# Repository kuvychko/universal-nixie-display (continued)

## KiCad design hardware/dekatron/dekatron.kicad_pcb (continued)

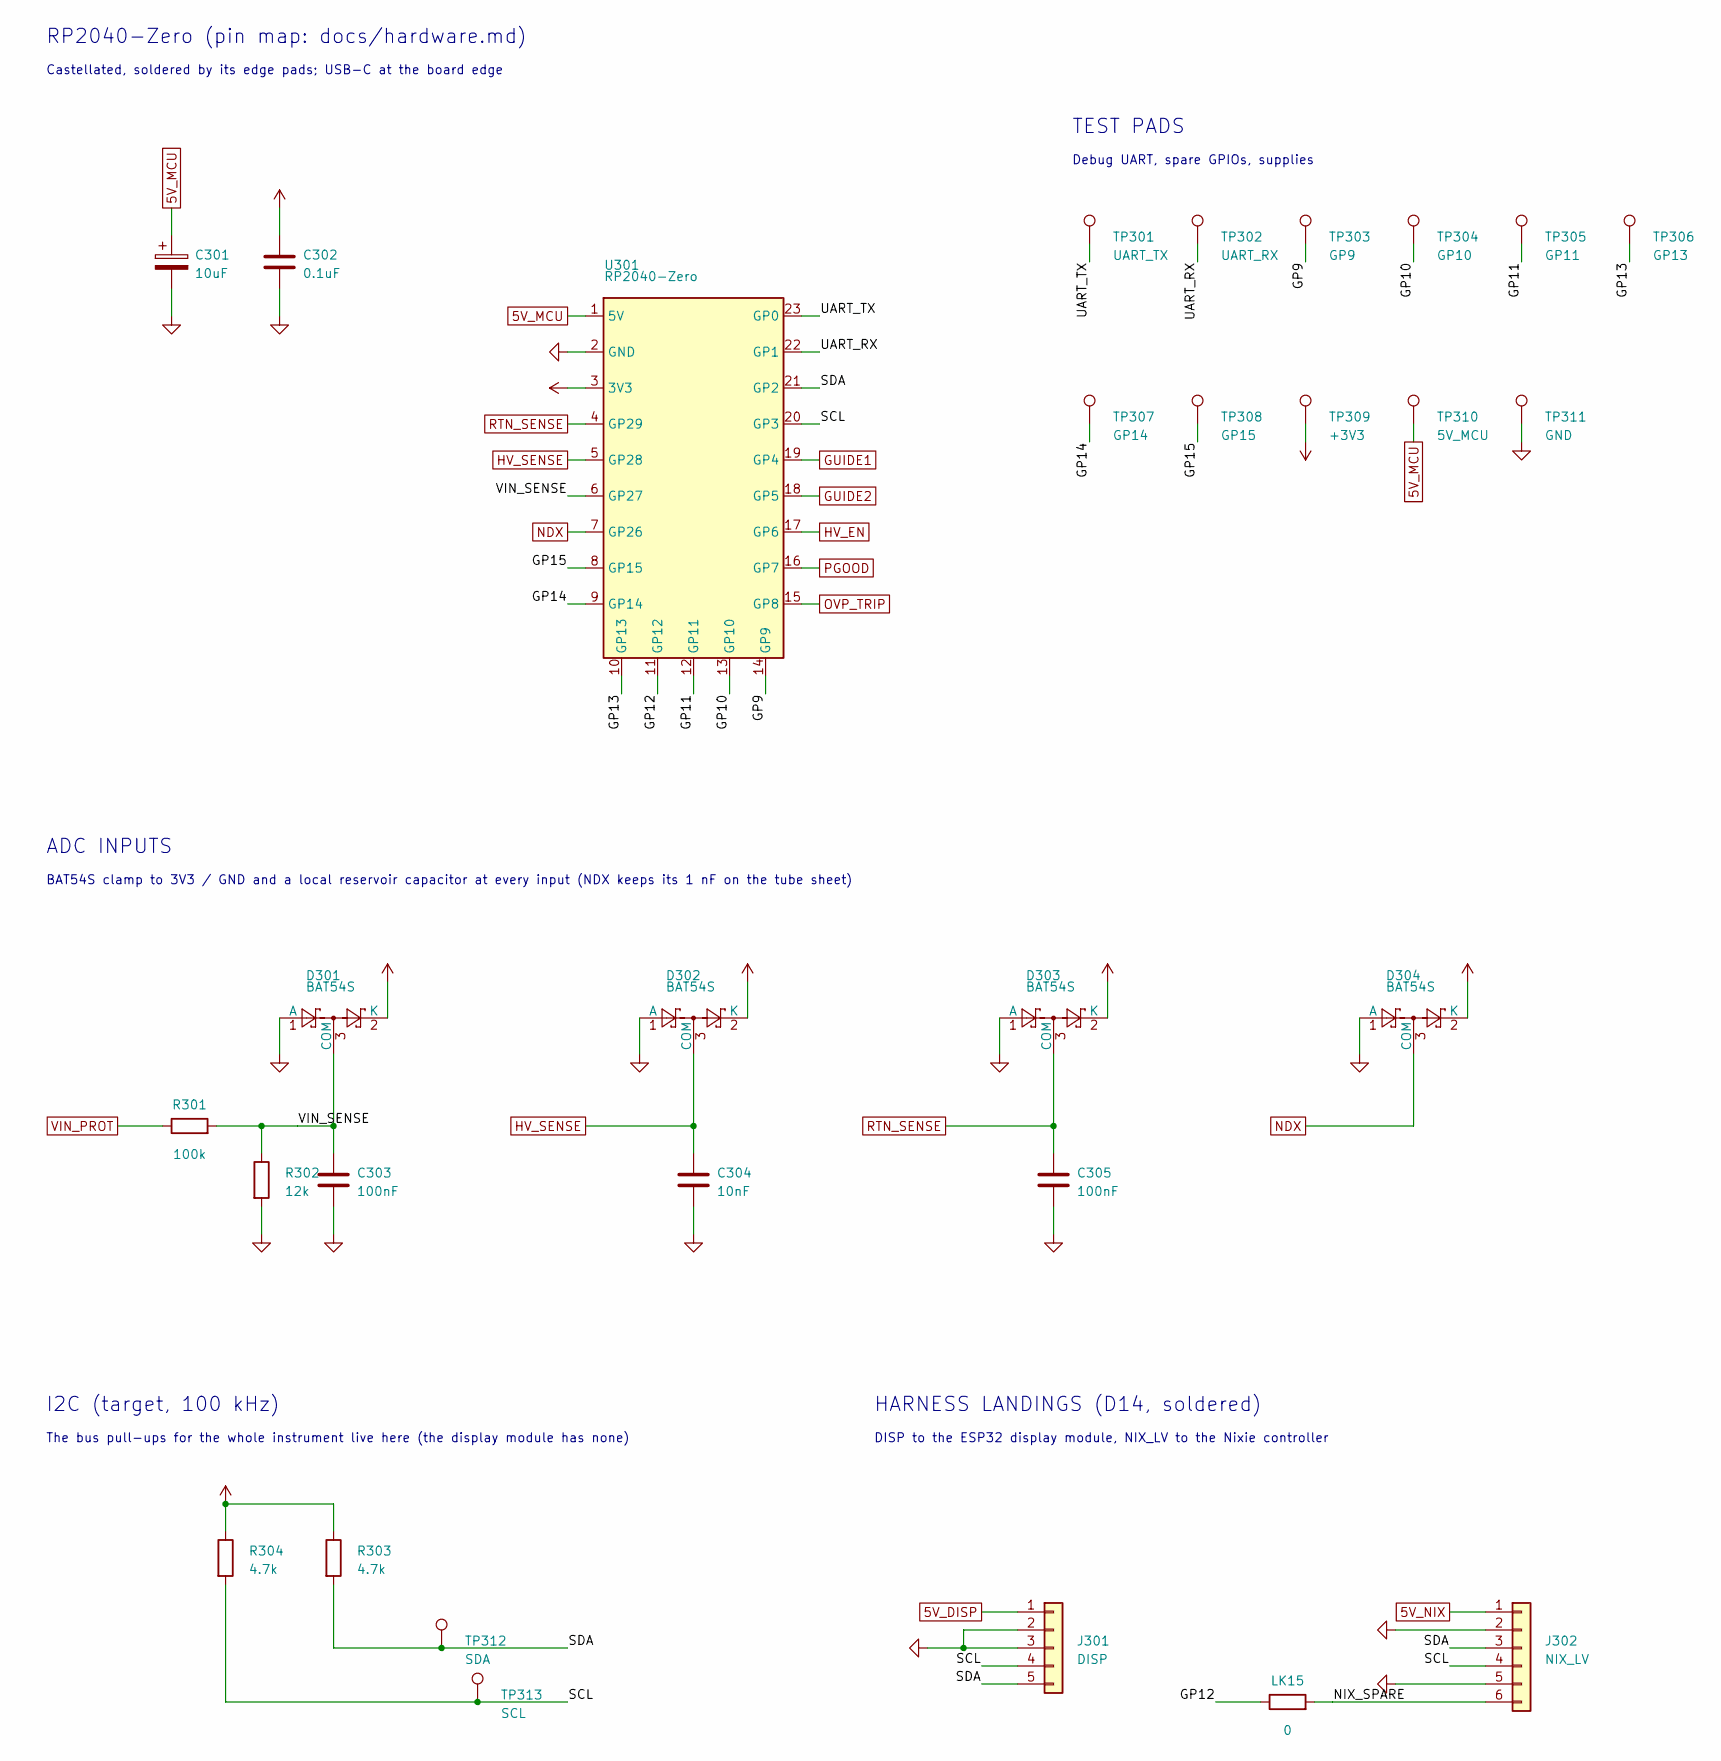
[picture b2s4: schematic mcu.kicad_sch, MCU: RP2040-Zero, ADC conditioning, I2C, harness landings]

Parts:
C301: 10uF; CP_EIA-3216-18_Kemet-A; Rating 16 V tantalum, 1.5 ohm ESR; MPN F911C106MAAAJ6
C302: 0.1uF; C_1206_3216Metric; Rating 50 V X7R; MPN CC1206JPX7R9BB104
C303, C305: 100nF; C_1206_3216Metric; Rating 25 V X7R; MPN CC1206JPX7R9BB104
C304: 10nF; C_1206_3216Metric; Rating 25 V X7R; MPN 12063C103JAT2A
D301, D302, D303, D304: BAT54S; SOT-23; Rating 30 V Schottky pair; MPN BAT54S RFG
J301: DISP; SolderWire-0.5sqmm_1x05_P4.8mm_D0.9mm_OD2.3mm
J302: NIX_LV; SolderWire-0.5sqmm_1x06_P4.8mm_D0.9mm_OD2.3mm
LK15: 0; R_1206_3216Metric
R301: 100k; R_1206_3216Metric
R302: 12k; R_1206_3216Metric; Rating 1 %; MPN ERJ-8ENF1202V
R303, R304: 4.7k; R_1206_3216Metric
TP301: UART_TX; TestPoint_THTPad_D1.5mm_Drill0.7mm
TP302: UART_RX; TestPoint_THTPad_D1.5mm_Drill0.7mm
TP303: GP9; TestPoint_THTPad_D1.5mm_Drill0.7mm
TP304: GP10; TestPoint_THTPad_D1.5mm_Drill0.7mm
TP305: GP11; TestPoint_THTPad_D1.5mm_Drill0.7mm
TP306: GP13; TestPoint_THTPad_D1.5mm_Drill0.7mm
TP307: GP14; TestPoint_THTPad_D1.5mm_Drill0.7mm
TP308: GP15; TestPoint_THTPad_D1.5mm_Drill0.7mm
TP309: +3V3; TestPoint_THTPad_D1.5mm_Drill0.7mm
TP310: 5V_MCU; TestPoint_THTPad_D1.5mm_Drill0.7mm
TP311: GND; TestPoint_THTPad_D1.5mm_Drill0.7mm
TP312: SDA; TestPoint_THTPad_D1.5mm_Drill0.7mm
TP313: SCL; TestPoint_THTPad_D1.5mm_Drill0.7mm
U301: RP2040-Zero; RP2040-Zero_Castellated; Rating headerless, castellated; MPN RP2040-Zero

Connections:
5V_DISP: J301.1; also elsewhere on the board
5V_MCU: C301.1, TP310.1, U301.1 (5V); also elsewhere on the board
5V_NIX: J302.1; also elsewhere on the board
+3V3: C302.1, D301.2 (K), D302.2 (K), D303.2 (K), D304.2 (K), R303.1, R304.1, TP309.1, U301.3 (3V3); also elsewhere on the board
/mcu/GP9: TP303.1, U301.14 (GP9)
/mcu/GP10: TP304.1, U301.13 (GP10)
/mcu/GP11: TP305.1, U301.12 (GP11)
/mcu/GP12: LK15.1, U301.11 (GP12)
/mcu/GP13: TP306.1, U301.10 (GP13)
/mcu/GP14: TP307.1, U301.9 (GP14)
/mcu/GP15: TP308.1, U301.8 (GP15)
/mcu/NIX_SPARE: J302.6, LK15.2
/mcu/SCL: J301.4, J302.4, R304.2, TP313.1, U301.20 (GP3)
/mcu/SDA: J301.5, J302.3, R303.2, TP312.1, U301.21 (GP2)
/mcu/UART_RX: TP302.1, U301.22 (GP1)
/mcu/UART_TX: TP301.1, U301.23 (GP0)
/mcu/VIN_SENSE: C303.1, D301.3 (COM), R301.2, R302.1, U301.6 (GP27)
GND: C301.2, C302.2, C303.2, C304.2, C305.2, D301.1 (A), D302.1 (A), D303.1 (A), D304.1 (A), J301.2, J301.3, J302.2, J302.5, R302.2, TP311.1, U301.2 (GND); also elsewhere on the board
GUIDE1: U301.19 (GP4); also elsewhere on the board
GUIDE2: U301.18 (GP5); also elsewhere on the board
HV_EN: U301.17 (GP6); also elsewhere on the board
HV_SENSE: C304.1, D302.3 (COM), U301.5 (GP28); also elsewhere on the board
NDX: D304.3 (COM), U301.7 (GP26); also elsewhere on the board
OVP_TRIP: U301.15 (GP8); also elsewhere on the board
PGOOD: U301.16 (GP7); also elsewhere on the board
RTN_SENSE: C305.1, D303.3 (COM), U301.4 (GP29); also elsewhere on the board
VIN_PROT: R301.1; also elsewhere on the board

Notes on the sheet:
RP2040-Zero (pin map: docs/hardware.md)
Castellated, soldered by its edge pads; USB-C at the board edge
TEST PADS
Debug UART, spare GPIOs, supplies
ADC INPUTS
BAT54S clamp to 3V3 / GND and a local reservoir capacitor at every input (NDX keeps its 1 nF on the tube sheet)
I2C (target, 100 kHz)
The bus pull-ups for the whole instrument live here (the display module has none)
HARNESS LANDINGS (D14, soldered)
DISP to the ESP32 display module, NIX_LV to the Nixie controller

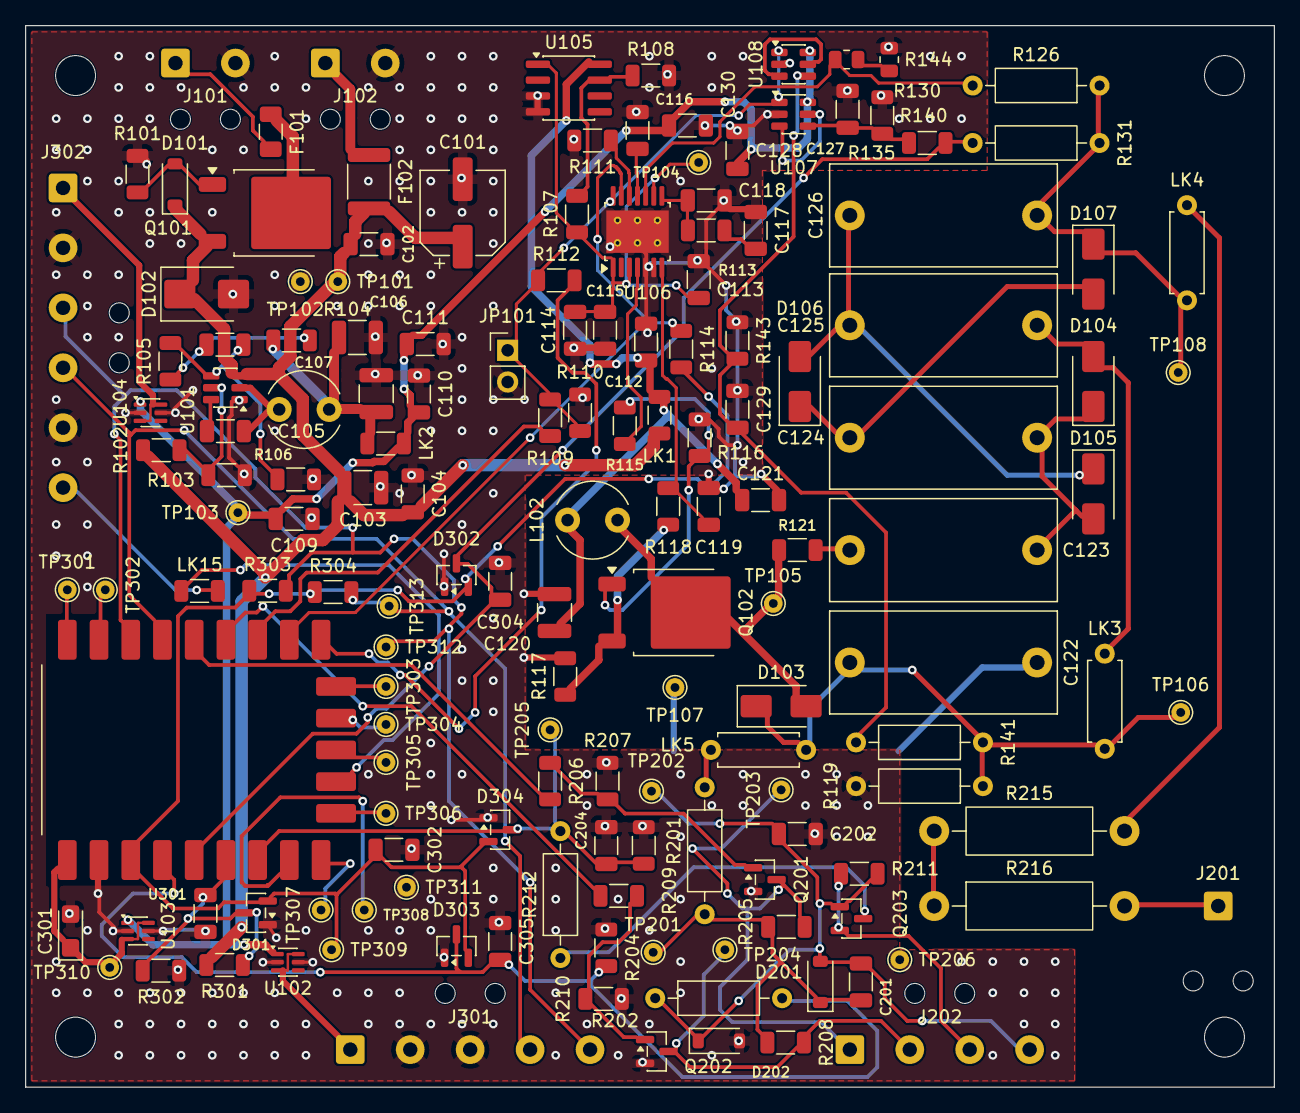
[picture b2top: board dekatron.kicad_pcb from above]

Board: 2 copper layers, 100.0 x 85.0 mm, 165 parts (0 on the bottom side), 76 nets.

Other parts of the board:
H1, H2, H3, H4: MountingHole_3.2mm_M3
TIE_J101, TIE_J102, TIE_J201, TIE_J202, TIE_J301, TIE_J302: cable tie

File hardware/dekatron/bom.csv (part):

Reference,Value,Function,Manufacturer,MPN,Rating,Footprint,Fit
C101,100uF 35V,"Input bulk, damps hot-plug ringing",Panasonic,EEE-FK1V101XP,"35 V, 340 mohm ESR",Capacitor_SMD:CP_Elec_6.3x7.7,
C102,0.1uF,Input HF bypass,Yageo,CC1206JPX7R9BB104,50 V X7R,Capacitor_SMD:C_1206_3216Metric,
C103,10uF 35V,Buck input,Yageo,CC1210KKX7RGBB106,35 V X7R,Capacitor_SMD:C_1210_3225Metric,
C104,0.1uF,Buck input HF,Yageo,CC1206JPX7R9BB104,50 V X7R,Capacitor_SMD:C_1206_3216Metric,
C105,0.1uF,Buck bootstrap,Yageo,CC1206JPX7R9BB104,25 V X7R,Capacitor_SMD:C_1206_3216Metric,
C106,22uF 25V,Buck output,Taiyo Yuden,MBAST32MSB7226KPNA18,25 V X7R,Capacitor_SMD:C_1210_3225Metric,
C107,22uF 25V,Buck output,Taiyo Yuden,MBAST32MSB7226KPNA18,25 V X7R,Capacitor_SMD:C_1210_3225Metric,
C108,75pF,Buck feed-forward,KYOCERA AVX,12065A750JAT2A,50 V C0G,Capacitor_SMD:C_1206_3216Metric,
C109,0.1uF,U102 input bypass,Yageo,CC1206JPX7R9BB104,50 V X7R,Capacitor_SMD:C_1206_3216Metric,
C110,0.1uF,U103 input bypass,Yageo,CC1206JPX7R9BB104,50 V X7R,Capacitor_SMD:C_1206_3216Metric,
C111,0.1uF,U104 input bypass,Yageo,CC1206JPX7R9BB104,50 V X7R,Capacitor_SMD:C_1206_3216Metric,
C112,1uF 35V,LDO input,KYOCERA AVX,1206DC105MAT2A,35 V X7R,Capacitor_SMD:C_1206_3216Metric,
C113,2.2uF,LDO output,Yageo,CS1206KKX7R8BB225,25 V X7R,Capacitor_SMD:C_1206_3216Metric,
C114,1uF,LM5156 BIAS/VCC bypass,KYOCERA AVX,1206DC105MAT2A,25 V X7R,Capacitor_SMD:C_1206_3216Metric,
C115,0.1uF,LM5156 BIAS/VCC HF,Yageo,CC1206JPX7R9BB104,50 V X7R,Capacitor_SMD:C_1206_3216Metric,
C116,47nF,Soft-start,Yageo,CC1206KRX7R8BB473,25 V X7R,Capacitor_SMD:C_1206_3216Metric,
C117,10nF,Compensation C,KYOCERA AVX,12063C103JAT2A,25 V X7R,Capacitor_SMD:C_1206_3216Metric,
C118,100pF,Compensation HF,KEMET,C1206C101K5GAC7210,50 V C0G,Capacitor_SMD:C_1206_3216Metric,
C119,470pF,CS filter C (pump surge),Walsin,1206B471K500CT,50 V C0G,Capacitor_SMD:C_1206_3216Metric,
C120,10uF 35V,Boost input,Yageo,CC1210KKX7RGBB106,35 V X7R,Capacitor_SMD:C_1210_3225Metric,
C121,0.1uF,Boost input HF,Yageo,CC1206JPX7R9BB104,50 V X7R,Capacitor_SMD:C_1206_3216Metric,
C122,0.47uF 400V,Tripler stack C1 (V_b),WIMA,MKS4G034704F00MSSD,400 V PET film,Capacitor_THT:C_Rect_L18.0mm_W8.0mm_P15.00mm_FKS3_FKP3,
C123,0.47uF 400V,Tripler pump CP1,WIMA,MKS4G034704F00MSSD,400 V PET film,Capacitor_THT:C_Rect_L18.0mm_W8.0mm_P15.00mm_FKS3_FKP3,
C124,0.47uF 400V,Tripler pump CP2,WIMA,MKS4G034704F00MSSD,400 V PET film,Capacitor_THT:C_Rect_L18.0mm_W8.0mm_P15.00mm_FKS3_FKP3,
C125,0.47uF 400V,Tripler stack C2,WIMA,MKS4G034704F00MSSD,400 V PET film,Capacitor_THT:C_Rect_L18.0mm_W8.0mm_P15.00mm_FKS3_FKP3,
C126,0.47uF 400V,Tripler stack C3,WIMA,MKS4G034704F00MSSD,400 V PET film,Capacitor_THT:C_Rect_L18.0mm_W8.0mm_P15.00mm_FKS3_FKP3,
C127,1nF,OVP sense filter,Walsin,1206N102K501CT,50 V C0G,Capacitor_SMD:C_1206_3216Metric,
C128,0.1uF,U107 bypass,Yageo,CC1206JPX7R9BB104,50 V X7R,Capacitor_SMD:C_1206_3216Metric,
C129,1nF,V_b OVP sense filter,Walsin,1206N102K501CT,50 V C0G,Capacitor_SMD:C_1206_3216Metric,
C130,0.1uF,U108 bypass,Yageo,CC1206JPX7R9BB104,50 V X7R,Capacitor_SMD:C_1206_3216Metric,
C201,0.1uF 100V,G+ to RTN bypass,Yageo,AC1206KKX7R0BB104,100 V X7R,Capacitor_SMD:C_1206_3216Metric,
C202,1uF 100V,RTN bypass: absorbs tube and guide current steps,KEMET,C1206C105M1RACAUTO,100 V X7R,Capacitor_SMD:C_1206_3216Metric,
C204,1nF,Index filter (tau 12 us),Walsin,1206N102K501CT,50 V C0G,Capacitor_SMD:C_1206_3216Metric,
C301,10uF,5V_MCU bulk at the module,KYOCERA AVX,F911C106MAAAJ6,"16 V tantalum, 1.5 ohm ESR",Capacitor_Tantalum_SMD:CP_EIA-3216-18_Kemet-A,
C302,0.1uF,3V3 bypass,Yageo,CC1206JPX7R9BB104,50 V X7R,Capacitor_SMD:C_1206_3216Metric,
C303,100nF,VIN_SENSE ADC sampling reservoir,Yageo,CC1206JPX7R9BB104,25 V X7R,Capacitor_SMD:C_1206_3216Metric,
C304,10nF,HV_SENSE ADC sampling reservoir,KYOCERA AVX,12063C103JAT2A,25 V X7R,Capacitor_SMD:C_1206_3216Metric,
C305,100nF,RTN_SENSE ADC sampling reservoir,Yageo,CC1206JPX7R9BB104,25 V X7R,Capacitor_SMD:C_1206_3216Metric,
D101,BZT52C10,"Q101 gate-source clamp, -10 V",Diotec Semiconductor,BZT52C10,,Diode_SMD:D_SOD-123,
D102,SMBJ15A,"Input TVS, unidirectional",Semtech,SMBJ15A,"15 V standoff, 24.4 V clamp",Diode_SMD:D_SMB,
D103,ES1J,Boost diode,Diotec Semiconductor,ES1J,"600 V, 1 A, 35 ns",Diode_SMD:D_SMA,
D104,ES1J,Tripler diode,Diotec Semiconductor,ES1J,"600 V, 1 A, 35 ns",Diode_SMD:D_SMA,
D105,ES1J,Tripler diode,Diotec Semiconductor,ES1J,"600 V, 1 A, 35 ns",Diode_SMD:D_SMA,
D106,ES1J,Tripler diode,Diotec Semiconductor,ES1J,"600 V, 1 A, 35 ns",Diode_SMD:D_SMA,
D107,ES1J,Tripler diode,Diotec Semiconductor,ES1J,"600 V, 1 A, 35 ns",Diode_SMD:D_SMA,
D201,39V,G+ above RTN: guide bias 39 V,Taiwan Semiconductor,MMSZ5259BH RHG,"39 V, 500 mW",Diode_SMD:D_SOD-123,
D202,51V,RTN shunt regulator: sinks tube current,onsemi,MMSZ5262BT1G,"51 V, 500 mW",Diode_SMD:D_SOD-123,
D301,BAT54S,VIN_SENSE clamp to 3V3 / GND,Taiwan Semiconductor,BAT54S RFG,30 V Schottky pair,Package_TO_SOT_SMD:SOT-23,
D302,BAT54S,HV_SENSE clamp to 3V3 / GND,Taiwan Semiconductor,BAT54S RFG,30 V Schottky pair,Package_TO_SOT_SMD:SOT-23,
D303,BAT54S,RTN_SENSE clamp to 3V3 / GND,Taiwan Semiconductor,BAT54S RFG,30 V Schottky pair,Package_TO_SOT_SMD:SOT-23,
D304,BAT54S,NDX clamp to 3V3 / GND,Taiwan Semiconductor,BAT54S RFG,30 V Schottky pair,Package_TO_SOT_SMD:SOT-23,
F101,2A Slo-Blo,Input fuse,Littelfuse,0468002.NRHF,"2 A, 63 V, I2t 0.506 A2s",Fuse:Fuse_1206_3216Metric,
F102,0.75A,Nixie HV module branch fuse,Littelfuse,1812L075/33DR,"0.75 A hold, 33 V",Fuse:Fuse_1812_4532Metric,
J101,PWR_IN,Harness landing PWR_IN: +12V_IN from panel switch / barrel jack; GND,,,,Connector_Wire:SolderWire-0.5sqmm_1x02_P4.8mm_D0.9mm_OD2.3mm,
J102,NIX_12V,Harness landing NIX_12V to the purchased Nixie HV module,,,,Connector_Wire:SolderWire-0.5sqmm_1x02_P4.8mm_D0.9mm_OD2.3mm,
J201,TUBE_ANODE,"Tube harness: anode (pin 8), 600 V wire, kept >= 3 mm from other pads",,,,Connector_Wire:SolderWire-0.5sqmm_1x01_D0.9mm_OD2.3mm,
J202,TUBE,"Tube harness: G1 (pin 5), G2 (10), K1 index (13), RTN = K0, K2-K9 tied at the socket",,,,Connector_Wire:SolderWire-0.5sqmm_1x04_P4.8mm_D0.9mm_OD2.3mm,
J301,DISP,"Harness DISP: 5V (P1 5V), GND (P1 GND), GND (3V3-plug GND), SCL (IO18), SDA (IO27)",,,,Connector_Wire:SolderWire-0.5sqmm_1x05_P4.8mm_D0.9mm_OD2.3mm,
J302,NIX_LV,Harness NIX_LV to the Nixie controller board,,,,Connector_Wire:SolderWire-0.5sqmm_1x06_P4.8mm_D0.9mm_OD2.3mm,
JP101,HV_INHIBIT,HV inhibit jumper (D11): shunt fitted holds EN/UVLO low,,,,Connector_PinHeader_2.54mm:PinHeader_1x02_P2.54mm_Vertical,
L101,15uH,Buck inductor,,"(kit, 6 x 8 mm radial)",Rated 1.31 A; limits the 5 V rail to ~1.3 A,Inductor_THT:L_Radial_D6.0mm_P4.00mm,
L102,100uH,HV boost inductor,,"(kit, 6 x 8 mm radial)","Rated 0.71 A, DCR 0.35 ohm, 4 mm pitch",Inductor_THT:L_Radial_D6.0mm_P4.00mm,
LK1,0,"D11 link L1: 12 V to the HV section (0 ohm, remove to open)",,,,Resistor_SMD:R_1206_3216Metric,
LK2,0,"D11 link L2: buck output to board 5 V (0 ohm, remove to open)",,,,Resistor_SMD:R_1206_3216Metric,
LK3,LINK,"D11 link L3: V_b to the tripler DC column (fault isolation; never powered open) (wire link, desolder to open)",,,,Resistor_THT:R_Axial_DIN0207_L6.3mm_D2.5mm_P7.62mm_Horizontal,
LK4,LINK,"D11 link L4: tripler output to the anode string (wire link, desolder to open)",,,,Resistor_THT:R_Axial_DIN0207_L6.3mm_D2.5mm_P7.62mm_Horizontal,
LK5,LINK,"D11 link L5: V_b to the G+/RTN regulators (wire link, desolder to open)",,,,Resistor_THT:R_Axial_DIN0207_L6.3mm_D2.5mm_P7.62mm_Horizontal,
LK15,0,"GP12 to the NIX_LV spare wire (0 ohm, fit when used)",,,,Resistor_SMD:R_1206_3216Metric,
Q101,IPD50P04P4L-11,Reverse-polarity protection,Infineon,IPD50P04P4L11ATMA2,"-40 V, 10.6 mohm, 200 A pulsed, VGS +5/-16 V",Package_TO_SOT_SMD:TO-252-2,
Q102,IPD70R1K4P7S,HV boost switch,Infineon,IPD70R1K4P7SAUMA1,"700 V, 1.4 ohm at 10 V, VGS +/-16 V",Package_TO_SOT_SMD:TO-252-2,
Q201,MMBTA42,Guide 1 driver,Diotec Semiconductor,MMBTA42,300 V NPN,Package_TO_SOT_SMD:SOT-23,
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
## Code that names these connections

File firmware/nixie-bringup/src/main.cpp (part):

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#include <Adafruit_NeoPixel.h>
#include <Wire.h>

static const uint8_t PIN_NIX12_EN = 0;  // Q102 base -> Q101 gate; R104 holds it off in reset
static const uint8_t PIN_SPARE = 1;     // NIX_SPARE, hardware pull-down; read only
static const uint8_t PIN_MAIN_SDA = 2;  // main bus (I2C1 target in the product): left as inputs
static const uint8_t PIN_MAIN_SCL = 3;
static const uint8_t PIN_WWVB_SDA = 4;  // I2C0, ES100 only (10k pull-ups on the carrier)
static const uint8_t PIN_WWVB_SCL = 5;
static const uint8_t PIN_WWVB_EN = 6;   // R308 10k pull-down: ES100 in shutdown in reset
static const uint8_t PIN_WWVB_IRQ = 7;  // R307 10k pull-up, active low
static const uint8_t PIN_BL = 8;        // DRV_BL via U302; R301 / R310 pull-downs: dark in reset
static const uint8_t PIN_LE = 9;        // DRV_LE via U302: high loads the latches
static const uint8_t PIN_CLK = 10;      // DRV_CLK via U302: the HV5622 shifts on the falling edge
static const uint8_t PIN_DATA = 11;     // DRV_DATA via U302
static const uint8_t PIN_DOUT = 12;     // U203 DATA OUT through R314 / R315 (2.43-3.39 V high)
static const uint8_t PIN_ENC_A = 13;    // PEC11R filter, 10k pull-ups
static const uint8_t PIN_ENC_B = 14;
static const uint8_t PIN_ENC_SW = 15;
static const uint8_t PIN_LED = 16;      // module WS2812
static const uint8_t PIN_HV_SENSE = 26; // NIX_HV_SENSE: 1M / 12k, ratio 84.3
static const uint8_t PIN_SW12_SENSE = 27; // NIX12_SENSE: +12V_SW through 100k / 12k

static const float ADC_VREF = 3.3f;
static const float HV_SCALE = 1012.0f / 12.0f;
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    return (float)sum / samples * ADC_VREF / 4095.0f;
}

static float readHv() { return adcVolts(PIN_HV_SENSE, 4) * HV_SCALE; }
static float readSw12() { return adcVolts(PIN_SW12_SENSE, 4) * SW12_SCALE; }

static void setLed()
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
static void hvOff()
{
    digitalWrite(PIN_NIX12_EN, LOW);
    hvOn = false;
    setLed();
}
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                  (unsigned long)millis(), readHv(), peakHv, readSw12(), hvOn ? 1 : 0, fault, left, hvTrip,
                  chainOk ? 1 : 0, blDuty, (unsigned long)pwmHz);
    printFrame("frame", latched);
    Serial.printf(" enc_a=%d enc_b=%d enc_sw=%d wwvb_en=%d wwvb_irq=%d spare=%d\n", digitalRead(PIN_ENC_A),
                  digitalRead(PIN_ENC_B), digitalRead(PIN_ENC_SW), digitalRead(PIN_WWVB_EN),
                  digitalRead(PIN_WWVB_IRQ), digitalRead(PIN_SPARE));
}

// ---- commands -----------------------------------------------------------------------------------------
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    onForMs = (millis() - onAtMs) + s * 1000; // "on" while on restarts the timer
    hvOn = true;
    setLed();
    digitalWrite(PIN_NIX12_EN, HIGH);
    Serial.printf("OK on %lu s\n", (unsigned long)s);
}

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static void startWire()
{
    if (!wireStarted) {
        Wire.setSDA(PIN_WWVB_SDA);
        Wire.setSCL(PIN_WWVB_SCL);
        Wire.setClock(100000); // 100 kHz: R305 / R306 not fitted, carrier 10k only (hardware.md)
        Wire.begin();
        wireStarted = true;
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static void cmdEs100()
{
    startWire();
    digitalWrite(PIN_WWVB_EN, HIGH);
    waitMs(ES100_WAKE_MS);
    int irqOn = digitalRead(PIN_WWVB_IRQ);
    int id = es100Read(ES100_REG_ID);
    digitalWrite(PIN_WWVB_EN, LOW);
    waitMs(10);
    int idOff = es100Read(ES100_REG_ID);
    Serial.printf("OK es100 en1: id=%s%02x%s irq=%d en0: %s\n", id < 0 ? "none" : "0x", id < 0 ? 0 : id,
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        Serial.println("ERR wen <0|1>");
        return;
    }
    digitalWrite(PIN_WWVB_EN, arg[0] == '1' ? HIGH : LOW);
    Serial.printf("OK wen %s\n", arg);
}

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{
    // 12 V switch off and tubes blanked before anything else; the reset pull-downs held them
    // until now. LE idles low (latches hold), CLK and DATA low.
    digitalWrite(PIN_NIX12_EN, LOW);
    pinMode(PIN_NIX12_EN, OUTPUT);
    digitalWrite(PIN_BL, LOW);
    pinMode(PIN_BL, OUTPUT);
    digitalWrite(PIN_LE, LOW);
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    pinMode(PIN_CLK, OUTPUT);
    digitalWrite(PIN_DATA, LOW);
    pinMode(PIN_DATA, OUTPUT);
    digitalWrite(PIN_WWVB_EN, LOW);
    pinMode(PIN_WWVB_EN, OUTPUT);
    // Inputs without the RP2040's default pulls: each has its own pull on the board, and the
    // main-bus pins must not load SDA / SCL.
    static const uint8_t inputs[] = {PIN_SPARE, PIN_MAIN_SDA, PIN_MAIN_SCL, PIN_WWVB_IRQ,
                                     PIN_DOUT,  PIN_ENC_A,    PIN_ENC_B,    PIN_ENC_SW};
    for (uint8_t p : inputs) {
        pinMode(p, INPUT);
    }
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
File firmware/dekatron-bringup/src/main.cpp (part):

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#include <Adafruit_NeoPixel.h>
#include <hardware/adc.h>

static const uint8_t PIN_GUIDE1 = 4;     // G1 driver base (D8); R_BE holds it off in reset
static const uint8_t PIN_GUIDE2 = 5;     // G2 driver base
static const uint8_t PIN_HV_EN = 6;      // LM5156 EN/UVLO through R109; R110 pull-down (D7)
static const uint8_t PIN_PGOOD = 7;      // LM5156 PGOOD, 10k pull-up to 3V3
static const uint8_t PIN_EN_NODE = 8;    // OVP_TRIP: reads the EN/UVLO node through R112
static const uint8_t PIN_VIN_SENSE = 27; // 100k / 12k
static const uint8_t PIN_HV_SENSE = 28;  // 2.7M / (7.87k + 6.2k): HV / 192.9
static const uint8_t PIN_NDX = 26;       // index level shifter output: 2.67-2.95 V with the glow on K1
static const uint8_t PIN_RTN_SENSE = 29; // 200k / 10k: RTN / 21
static const uint8_t PIN_LED = 16;       // module WS2812

static const float ADC_VREF = 3.3f;
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
static const uint32_t ON_DEFAULT_S = 10;
static const uint32_t ON_MAX_S = 300;
static const uint32_t EN_BLANK_MS = 2;   // EN node settles after HV_EN rises
static const uint32_t WDT_MS = 500;

// Step limits: plan section 5 budgets <= 200 steps/s. The phase limits are only sanity bounds;
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    return (float)sum / samples * ADC_VREF / 4095.0f;
}

static float readVin() { return adcVolts(PIN_VIN_SENSE, 8) * VIN_SCALE; }
static float readHv() { return adcVolts(PIN_HV_SENSE, 8) * HV_SCALE; }
static float readRtn() { return adcVolts(PIN_RTN_SENSE, 8) * RTN_SCALE; }
static float readNdx() { return adcVolts(PIN_NDX, 4); }

static void guidesRest()
{
    digitalWrite(PIN_GUIDE1, LOW);
    digitalWrite(PIN_GUIDE2, LOW);
    stepsLeft = 0;
    ndxPending = false;
}
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
static void hvOff()
{
    digitalWrite(PIN_HV_EN, LOW);
    hvOn = false;
    guidesRest();
    setLed(false);
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    float left = hvOn ? (onForMs - (millis() - onAtMs)) / 1000.0f : 0.0f;
    Serial.printf("OK t_ms=%lu vin=%.2f hv=%.1f peak=%.1f pgood=%d en_node=%d hv_en=%d fault=%s left=%.1f "
                  "rtn=%.1f ndx=%.2f g1=%d g2=%d steps_left=%lu steps_done=%lu ndx_hits=%lu\n",
                  (unsigned long)millis(), readVin(), readHv(), peakHv, digitalRead(PIN_PGOOD),
                  digitalRead(PIN_EN_NODE), hvOn ? 1 : 0, fault, left, readRtn(), readNdx(),
                  digitalRead(PIN_GUIDE1), digitalRead(PIN_GUIDE2), (unsigned long)stepsLeft,
                  (unsigned long)stepsDone, (unsigned long)ndxHits);
}

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    onForMs = s * 1000;
    hvOn = true;
    setLed(true);
    digitalWrite(PIN_HV_EN, HIGH);
    Serial.printf("OK on %lu s\n", (unsigned long)s);
}

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        return;
    }
    // GPIO high turns the driver on: the guide is pulled from G+ to ~0 V.
    digitalWrite(g == 1 ? PIN_GUIDE1 : PIN_GUIDE2, on ? HIGH : LOW);
    Serial.printf("OK guide %lu %s\n", (unsigned long)g, on ? "on" : "rest");
}

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// One step, blocking for 3 x phaseUs (<= 6 ms, well inside the watchdog).
static void stepOnce()
{
    uint8_t first = stepFwd ? PIN_GUIDE1 : PIN_GUIDE2;
    uint8_t second = stepFwd ? PIN_GUIDE2 : PIN_GUIDE1;
    digitalWrite(first, HIGH);
    delayMicroseconds(phaseUs);
    digitalWrite(second, HIGH);
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    }

    guidesRest();
    uint8_t first = strcmp(dir, "fwd") == 0 ? PIN_GUIDE1 : PIN_GUIDE2;
    uint8_t second = first == PIN_GUIDE1 ? PIN_GUIDE2 : PIN_GUIDE1;
    const uint32_t mask = (1u << first) | (1u << second);
    uint32_t value[4];
    for (int i = 0; i < nEdges; i++) {
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
    uint32_t hits = 0;
    bool overflow = false;
    uint32_t slipMax = 0;   // lateness of guide edges and NDX samples within a step
    uint32_t startLate = 0; // lateness of a step's first edge: the previous step's work overran
    uint32_t workMax = 0;   // NDX sample plus per-step checks, us: the rest time this needs
    uint32_t pgoodLow = 0;
    // The hot loop uses the SDK directly (gpio_put/gpio_get/adc_read): digitalWrite, analogRead and
    // Serial.available() cost enough per step to slip the timetable by 46 us at 100 Hz (board 1,
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    const uint32_t ndxHighRaw = (uint32_t)(NDX_HIGH_V / ADC_VREF * 4095.0f);
    const uint32_t vinMinRaw = (uint32_t)(VIN_MIN / VIN_SCALE / ADC_VREF * 4095.0f);
    const uint32_t vinMaxRaw = (uint32_t)(VIN_MAX / VIN_SCALE / ADC_VREF * 4095.0f);
    adc_select_input(PIN_NDX - 26);
    uint32_t done = 0;
    const char *stop = "done";
    uint32_t t = time_us_32() + 1000;
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        slipMax = maxU32(slipMax, slip);
        t += period;

        if (!gpio_get(PIN_PGOOD)) {
            pgoodLow++;
        }
        if (!gpio_get(PIN_EN_NODE)) {
            adc_select_input(PIN_HV_SENSE - 26); // trip() prints HV via analogRead()
            trip("en_low");
            stop = "fault";
            break;
        }
        if ((done & 0x3F) == 0) {
            // Every 64 steps: VIN, the HV timer and the serial abort.
            adc_select_input(PIN_VIN_SENSE - 26);
            uint32_t vinRaw = adc_read();
            adc_select_input(PIN_NDX - 26);
            if (vinRaw < vinMinRaw || vinRaw > vinMaxRaw) {
                adc_select_input(PIN_HV_SENSE - 26); // trip() prints HV via analogRead()
                trip("vin");
                stop = "fault";
                break;
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    // analogRead() caches the mux (_lastADCMux) and skips adc_select_input() for the pin it read
    // last: hvPre's HV_SENSE. Put the mux back there, or the next HV reads return NDX x 192.9
    // (hv_post 549.6 V with the glow on K1, board 1, 2026-11-12).
    adc_select_input(PIN_HV_SENSE - 26);
    float hvPost = readHv();

    Serial.printf("OK sweep done n=%lu done=%lu stop=%s hits=%lu overflow=%d slip_max_us=%lu start_late_us=%lu "
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void setup()
{
    // HV off and guides at rest before anything else; the reset pull-downs held them until now.
    digitalWrite(PIN_HV_EN, LOW);
    pinMode(PIN_HV_EN, OUTPUT);
    digitalWrite(PIN_GUIDE1, LOW);
    digitalWrite(PIN_GUIDE2, LOW);
    pinMode(PIN_GUIDE1, OUTPUT);
    pinMode(PIN_GUIDE2, OUTPUT);
    pinMode(PIN_PGOOD, INPUT);
    pinMode(PIN_EN_NODE, INPUT); // no pull-down: it would load EN/UVLO (Phase 1B review item 4)
    analogReadResolution(12);
    // The first read of each ADC pin sets it up and comes back low (VIN 8.5 V for 11.9 V on
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    rp2040.wdt_reset();

    if (hvOn) {
        float hv = analogRead(PIN_HV_SENSE) * ADC_VREF / 4095.0f * HV_SCALE;
        if (hv > peakHv) {
            peakHv = hv;
        }
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        // (board 1, 2026-10-25). Read through the ADC: analogRead() turns off GP26's digital
        // input buffer, so digitalRead() would always return low.
        ndxPending = false;
        if (adcVolts(PIN_NDX, 1) > NDX_HIGH_V) {
            ndxHits++;
        }
        if (stepsLeft == 0) {
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        } else if ((int32_t)(now - logNextMs) >= 0) {
            logNextMs += logPeriodMs;
            Serial.printf("%lu,%.2f,%.1f,%d,%d,%d,%.1f,%.2f\n", (unsigned long)now, readVin(), readHv(),
                          digitalRead(PIN_PGOOD), digitalRead(PIN_EN_NODE), hvOn ? 1 : 0, readRtn(),
                          readNdx());
        }
    }
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
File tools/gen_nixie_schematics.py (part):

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)'''


# IN-14, tube-tester.com pinout (bottom view): 1 anode, 2 left decimal point, 3-11 digits 1-9,
# 12 digit 0, 13 right decimal point
IN14_CATHODES = [("LDP", "2"), ("0", "12")] + [(str(d), str(d + 2)) for d in range(1, 10)] + [("RDP", "13")]

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                 textpos=(10.16, 12.7),
                 fields=F("3.3 V -> 12 V for the HV5622 inputs", "CD40109BNSRE4", "TI",
                          "VCC/VDD 3-18 V, SOP-16 (NS) 5.3 mm"))
    for pin, net in (("3", "DRV_DATA"), ("6", "DRV_CLK"), ("10", "DRV_LE"), ("14", "DRV_BL")):
        lead(sh, u[pin], net, -2.54, 0)
    for pin, net in (("4", "DRV12_DATA"), ("5", "DRV12_CLK"), ("11", "DRV12_LE"), ("13", "DRV12_BL")):
        lead(sh, u[pin], net, 2.54, 0)
    bx = 162.56                                          # enables bus, tied to 3V3
    ens = [u[p] for p in ("2", "7", "9", "15")]
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
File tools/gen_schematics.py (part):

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    YE = M["EN/UVLO/SYNC"][1]
    rr = hR("R109", "10k", 91.44, YE, "HV_EN series resistor")
    sh.w(M["EN/UVLO/SYNC"], (129.54, YE), (121.92, YE), (114.3, YE), (106.68, YE), rr["2"])
    sh.nl("HV_EN_PIN", (129.54, YE))
    sh.w(rr["1"], (86.36, YE))
    sh.gl("HV_EN", (86.36, YE), 180)
    r = vR("R110", "100k", 121.92, YE + 3.81, "EN/UVLO pull-down: HV off by default (D7)")
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        sh.pwr("+5V", (x, u["V+"][1] - 2.54))
        down_gnd(u["V-"])
        sh.w(u["OUT"], (u["OUT"][0] + 7.62, y))
        sh.nl("HV_EN_PIN", (u["OUT"][0] + 7.62, y))
        return u

    comparator("U108", 340.36, VS[1] - 2.54, VS, 307.34, "VB_OVP_SENSE", "VB_OVP_REF", "C129", "V_b OVP",
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    sh.nl("TRP_P2", (106.68, YB))

    def top(ref, part, value, code, x, fn, dnp=False):
        """Single leaded high-voltage resistor hanging from the HV_STACK bus; returns its lower pin."""
        sh.w((x, YT), (x, YT + 5.08))
        r = v2(R, ref, value, x, YT + 5.08, F(fn, hhv(part["model"], code), part["mfr"], part["rating"]),
               part["fp"], dnp=dnp)
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        sh.gl(f"GUIDE{n}", (xc - 25.4, 96.52), 180)

    # ---- index sense: K1 lifts the MMBTA92 emitter above RTN; collector into the divider ----------
    note("INDEX SENSE (D9)", "MMBTA92 level shifter from K1 (pin 13); 220k / 13k -> ~2.9 V at NDX; clamp at the RP2040", 15.24, 142.24)
    q = sh.place("Transistor_BJT:Q_PNP_BEC", "Q203", "MMBTA92", 83.82, 167.64, mirror="x", footprint=FP_SOT23,
                 fields=F("Index level shifter", "MMBTA92", "Nexperia", "300 V PNP"))
    # RTN from the regulator down to the base
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    sh.w(rs[0]["2"], (185.42, 160.02), rs[1]["1"])
    sh.nl("STR_A1", (185.42, 160.02))
    j1 = sh.place("Connector_Generic:Conn_01x01", "J201", "TUBE_ANODE", 223.52, 160.02, footprint=FP_WIRE1,
                  fields=F("Tube harness: anode (pin 8), 600 V wire, kept >= 3 mm from other pads"))
    sh.w(rs[1]["2"], (208.28, 160.02), j1["1"])
    sh.nl("ANODE", (208.28, 160.02))
    jh = sh.place("Connector_Generic:Conn_01x04", "J202", "TUBE", 248.92, 96.52, footprint=FP_WIRE4,
                  fields=F("Tube harness: G1 (pin 5), G2 (10), K1 index (13), RTN = K0, K2-K9 tied at the socket"))
    for pin, name in (("1", "TUBE_G1"), ("2", "TUBE_G2"), ("3", "TUBE_K1"), ("4", "RTN")):
        e = jh[pin]
        sh.w(e, (e[0] - 10.16, e[1]))
        sh.nl(name, (e[0] - 10.16, e[1]), 180)
    sh.text("A101 socket: anode 8, G1 5, G2 10, K1 13;\nK0, K2-K9 (pins 1-4, 6, 7, 9, 11, 12) tied together onto RTN",
            205.74, 111.76, 1.27)
    sh.finish()
    return sh
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
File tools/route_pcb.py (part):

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VIA_DRILL = 0.35    # as pcb_io.py
TRK_MARG = 0.05     # extra margin against other nets' tracks: a thin diagonal's raster sits ~0.05 mm inside
                    # its real edge (DRC: a 1 mm VIN_PROT end 0.153 mm from a 0.25 mm PGOOD diagonal). Not
                    # for the LM5156 pin nets, whose escapes it walls in (PGOOD then fails)
PAD_MARG = 0.03     # extra margin against other nets' pads: a pad's raster can sit a cell inside its real
                    # outline, so a diagonal track grazing a pad corner came out 0.175-0.1875 mm (rule 0.2)
HOLE_GAP = 0.25     # drilled hole to drilled hole (board setup); vias keep it from every plated hole too
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# clearance, but on the 0.1 mm raster the halo (0.2 + 0.15 + MARG) equals the measured distance and
# the escape reads as blocked; 0.25 mm clears it (fab minimum 0.152 mm)
FINE = {"/power/LM5156_GATE", "/power/LM5156_CS", "/power/LM5156_COMP", "/power/LM5156_FB", "/power/LM5156_SS",
        "/power/LM5156_RT", "/power/VDRV", "PGOOD", "/power/HV_EN_PIN"}


def width(net):
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
# fine-pitch parts whose signal pins get a reserved escape stub (mm), and the stub width
FANOUT = {"U106": 1.0}
FANOUT_SKIP = {("U106", "8")}     # COMP leaves its end pin sideways to C118; a stub there pockets VDRV (pin 9)
STUB_W = 0.25
# Fixed pad-to-pad ties laid before routing, under a package body where no other net can reach. The
# LM66100s' CE (pin 3) joins VOUT (pin 6, the opposite corner): routed around the package it walled in
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
def order(nets):
    # the LM5156's fine-pitch pins first: any earlier net running past the pin tips seals them in
    # (12V_HV along the left row, HV_EN_PIN along the right row did exactly that)
    # EN last: its pin is top-left but its parts sit below-right, so on the top layer it can only cross
    # the whole row; routed last it must take a via
    # top row: RT / SS / FB (short, straight up to their parts), COMP (a 2 mm hop sideways from end pin 8
    # to C118), then VDRV, whose pin 9 sits between FB and COMP and must go around both
    fine = [n for n in ("/power/LM5156_GATE", "/power/LM5156_CS", "/power/LM5156_RT", "/power/LM5156_SS",
                        "/power/LM5156_FB", "/power/LM5156_COMP", "/power/VDRV", "PGOOD",
                        "/power/HV_EN_PIN") if n in nets]
    first = fine + [n for n in FIRST if n in nets and n not in fine]
    promoted = [n for n in PROMOTE if n in nets and n not in fine]       # after the LM5156 group
    first = fine + promoted + [n for n in first if n not in promoted and n not in fine]
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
